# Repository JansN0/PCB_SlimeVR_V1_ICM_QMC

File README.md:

# PCB_SlimeVR_V1_ICM_QMC
Version of SlimeVR

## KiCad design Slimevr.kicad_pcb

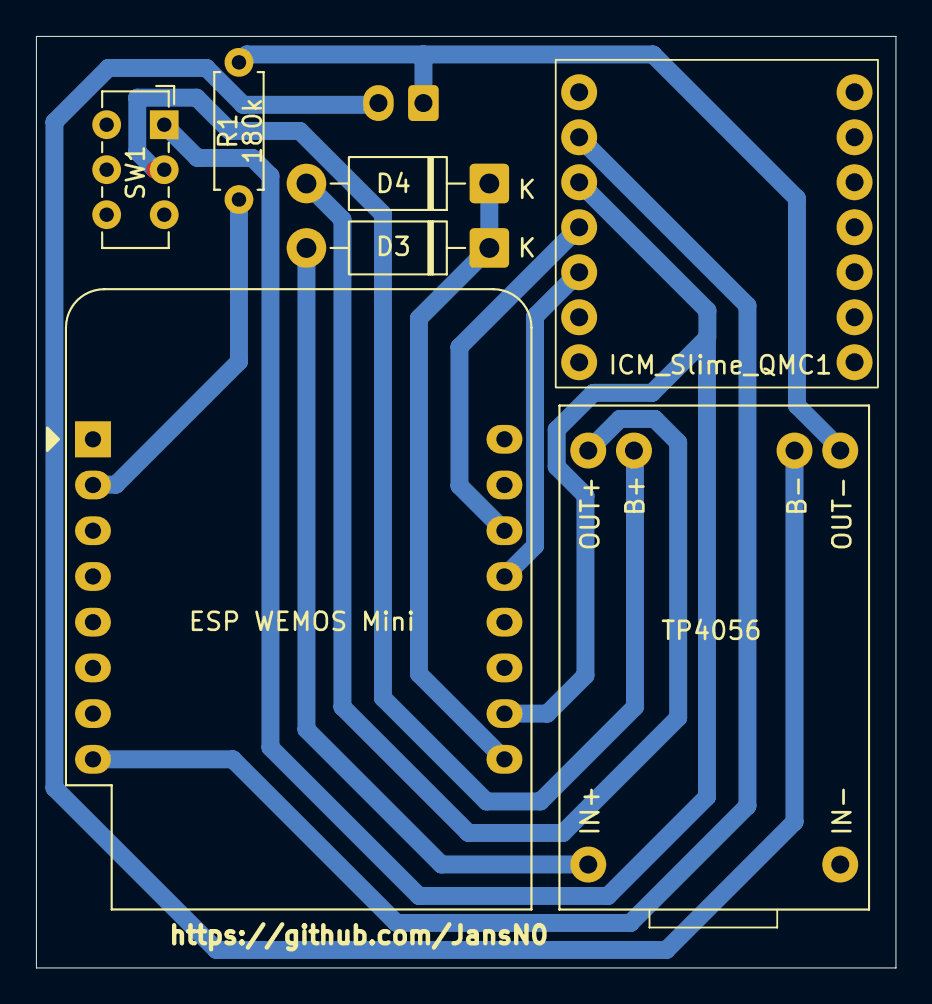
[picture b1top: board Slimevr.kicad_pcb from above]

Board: 2 copper layers, 47.8 x 51.8 mm, 8 parts (1 on the bottom side), 11 nets.

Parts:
D3, D4: 1N5817; D_DO-41_SOD81_P10.16mm_Horizontal
ESP WEMOS Mini: WEMOS_D1_mini; WEMOS_D1_mini_light
J1: Conn_01x02; JST_EH_B2B-EH-A_1x02_P2.50mm_Vertical
R1: 180k; R_Axial_DIN0207_L6.3mm_D2.5mm_P7.62mm_Horizontal
SW1: SW_SPST; SW_E-Switch_EG1271_SPDT
TP4056: TP4056; TP4056-Module
U1: ICM_Slime_QMC1; IC_ICM-45686

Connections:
unnamed: D3.2 (A), TP4056.1 (+IN)
unnamed: D3.1 (K), D4.1 (K), ESP WEMOS Mini.9 (5V)
unnamed: D4.2 (A), TP4056.3 (VOUT)
unnamed: J1.1, R1.2, TP4056.4 (+BAT)
unnamed: J1.2, TP4056.6 (GND)
unnamed: ESP WEMOS Mini.10 (GND), SW1.1 (A), U1.3 (GND)
unnamed: SW1.2 (B), TP4056.5 (-BAT)
unnamed: ESP WEMOS Mini.8 (3V3), U1.2 (3V3)
unnamed: ESP WEMOS Mini.14 (SCL/D1), U1.4 (SCL)
unnamed: ESP WEMOS Mini.13 (SDA/D2), U1.5 (SDA)
unnamed: ESP WEMOS Mini.2 (A0), R1.1
